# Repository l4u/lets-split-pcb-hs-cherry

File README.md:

# lets-split-pcb-hs-cherry

Let's Split PCB for holtite socket only Cherry MX switches.

Based on [climbalima/let-s-Split-v2](https://github.com/climbalima/let-s-Split-v2).

## Overview

By crimping the socket to the through hole, it is possible to install without having to solder the axis of the switch and Pro Micro.

Cherry MX switch and several clone switches are available.

ALPS/Matias switch is ***NOT AVAILABLE***.

## Supported socket

- [TE CONNECTIVITY 8134-HC-8P2](http://www.te.com/jpn-ja/product-7-1437514-0.html)
- [TE CONNECTIVITY 8134-HC-8P3](http://www.te.com/jpn-ja/product-7-1437514-1.html)

## How to order PCB

There is a [releases page](https://github.com/haru-ake/lets-split-pcb-hs-cherry/releases) that zipped the Gerber file. You can use it to order to your preferred merchant.

I ordered it for [PCBGOGO](https://www.pcbgogo.jp/) and confirmed that I could manufacture it.

## How to crimp the socket

See youtube video.

## Points to note when crimping

***IMPORTANT!*** Since Pro Micro will be inserted from the bottom of the PCB, the switch will be inserted from the top of the PCB, so be careful of the orientation of the PCB when crimping the socket.

### Pro Micro

You can crimp the socket only to the through hole of the pin to be used. You can ***NOT*** crimp the socket into the through hole of the unused pin.

#### Rev 1.1.0 or higher

#### Up to rev 1.0.1

It is not possible to crimp the socket to the through hole where the socket is not stuck in the picture.

### Switches

Be careful not to mistake the position of the through hole.

## IMPORTANT NOTE

1. I have not confirmed the operation of some functions. Refer to the [Confirmed list](https://github.com/haru-ake/lets-split-pcb-hs-cherry/wiki/Confirmed-list) for details.
1. With PCB revision 1.1.0 or higher, the board size has been changed. If you want to use the original case of Let's Split Be careful.

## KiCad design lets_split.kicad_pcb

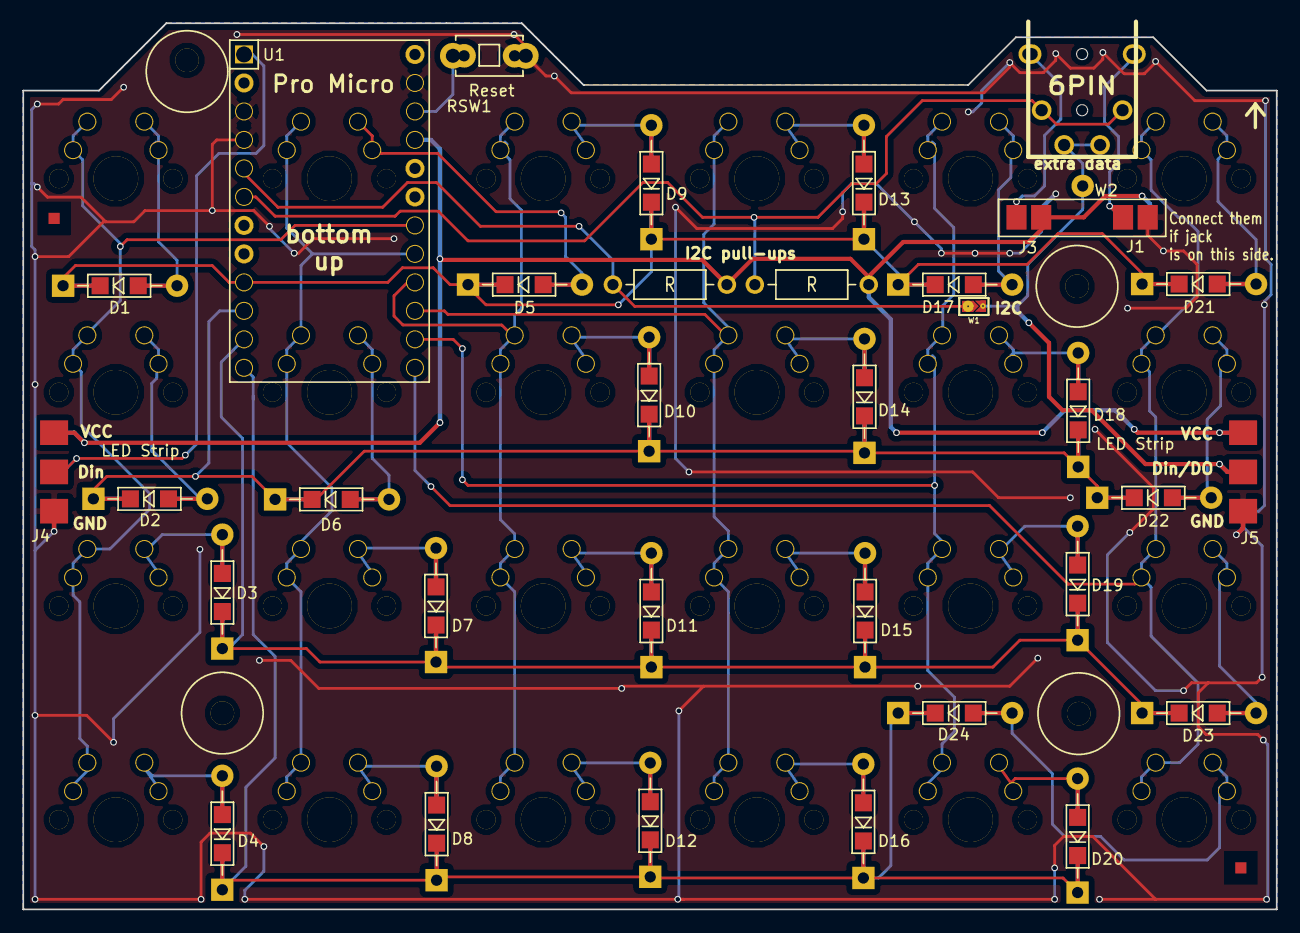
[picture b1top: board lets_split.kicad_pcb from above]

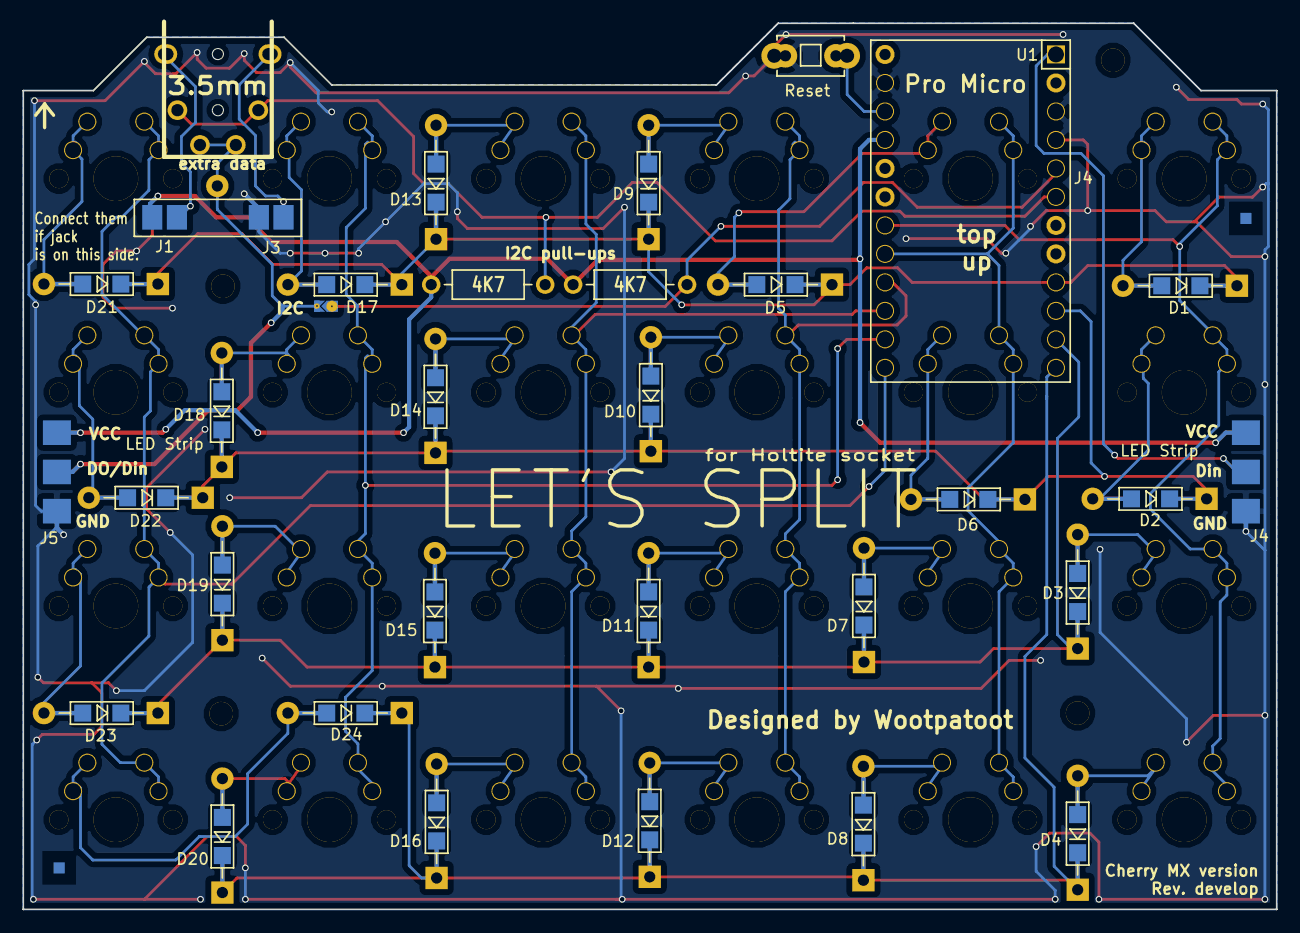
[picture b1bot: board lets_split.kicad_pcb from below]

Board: 2 copper layers, 111.8 x 79.0 mm, 67 parts (5 on the bottom side), 43 nets.

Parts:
D1, D2, D3, D4, D5, D6, D7, D8, D9, D10, D11, D12, D13, D14, D15, D16, D17, D18, D19, D20, D21, D22, D23, D24: D; Diode_TH_SOD123
J1, J3: 3PIN; SMD_JUMPER_2
J2: 6PIN; 4pin35mmAudio
J4, J5: 3PIN; CON3_SMD_BOTH
M1, M2, M3, M4: FIDUCIAL; Fiducial_Mark
R1, R2: 4K7; RESISTOR
RSW1: SW_PUSH; TACTILE_COMPATIBLE
SW1, SW2, SW3, SW4, SW5, SW6, SW7, SW8, SW9, SW10, SW11, SW12, SW13, SW14, SW15, SW16, SW17, SW18, SW19, SW20, SW21, SW22, SW23, SW24: SW_PUSH; MXALPS_FLIP_HOLES
U1: ProMicro
U2, U3, U4: HOLE
U5: HOLE; HOLE_2
W1: TEST; JUMPER_SMD_2DUB
W2: TEST_1P; SolderWirePad_single_2mmDrill

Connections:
GND: J1.1, J3.1, J4.3, J5.3, RSW1.2, U1.3, U1.4, U1.23
I2C_SDA: R1.2, U1.5, W1.2
unnamed: D1.2, SW1.2
unnamed: D2.2, SW2.2
unnamed: D3.2, SW3.2
unnamed: D4.2, SW4.2
unnamed: D5.2, SW5.2
unnamed: D6.2, SW6.2
unnamed: D7.2, SW7.2
unnamed: D8.2, SW8.2
unnamed: D9.2, SW9.2
unnamed: D10.2, SW10.2
unnamed: D11.2, SW11.2
unnamed: D12.2, SW12.2
unnamed: D13.2, SW13.2
unnamed: D14.2, SW14.2
unnamed: D15.2, SW15.2
unnamed: D16.2, SW16.2
unnamed: D17.2, SW17.2
unnamed: D18.2, SW18.2
unnamed: D19.2, SW19.2
unnamed: D20.2, SW20.2
unnamed: D21.2, SW21.2
unnamed: D22.2, SW22.2
unnamed: D23.2, SW23.2
unnamed: D24.2, SW24.2
unnamed: J1.2, J2.1
unnamed: J2.4, J3.2
unnamed: J4.2, U1.1
unnamed: RSW1.1, U1.22
VCC: J1.3, J3.3, J4.1, J5.1, R1.1, R2.2, U1.21
col0: SW1.1, SW2.1, SW3.1, SW4.1, U1.18
col1: SW5.1, SW6.1, SW7.1, SW8.1, U1.17
col2: SW9.1, SW10.1, SW11.1, SW12.1, U1.16
col3: SW13.1, SW14.1, SW15.1, SW16.1, U1.15
col4: SW17.1, SW18.1, SW19.1, SW20.1, U1.14
col5: SW21.1, SW22.1, SW23.1, SW24.1, U1.13
data: J2.2, J2.6, R2.1, U1.6
row0: D1.1, D5.1, D9.1, D13.1, D17.1, D21.1, U1.9
row1: D2.1, D6.1, D10.1, D14.1, D18.1, D22.1, U1.10
row2: D3.1, D7.1, D11.1, D15.1, D19.1, D23.1, U1.11
row3: D4.1, D8.1, D12.1, D16.1, D20.1, D24.1, U1.12
xtradata: J2.3, J2.5, J5.2, W1.1, W2.1

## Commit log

2017-08-25 add files
2017-08-25 remove cartoon characters protected by copyright
2017-08-25 add Makefile
2017-08-25 tweak positions
2017-08-30 adjust the size of through holes to mount switches to fit holtite socket
2017-08-30 tweak wires
2017-08-30 adjust the size of through holes to mount Pro Micro to fit holtite socket
2017-08-30 tweak holes size for fixing to the switch plate
2017-08-30 tweak filled zone
2017-08-30 make the minimum hole diameter 0.3mm
2017-08-30 add revision on PCB
2017-09-09 first release
2017-09-09 development version
2017-09-12 tweak hole position for fixing to the switch plate
2017-09-12 bump version to 1.0.1
2017-09-28 bump version to 1.1.0
2018-03-25 Use local holes and JUMPER_SMD_2DUB
2018-04-01 Update hole
2018-04-01 Use promicro without socket
2018-04-01 Refill zone
2018-04-01 Add universal switch; fix prettylib
2018-04-01 Remove fiducial marker
2018-04-01 Use universal footprint
2018-04-01 Move components and run autoroute
